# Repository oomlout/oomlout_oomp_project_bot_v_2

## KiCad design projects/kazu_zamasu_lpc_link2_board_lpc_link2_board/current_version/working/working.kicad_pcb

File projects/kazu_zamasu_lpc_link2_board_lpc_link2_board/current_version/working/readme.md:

# lpc_link2_board
 
## summary 
* id: kazu_zamasu_lpc_link2_board_lpc_link2_board
* user: kazu_zamasu
* name: lpc_link2_board
* board: lpc_link2_board
* repo: https://github.com/Kazu-zamasu/LPC-Link2-Board
* src_file_repo_kicad_pcb: LPC-Link2-Board.kicad_pcb
* src_file_repo_kicad_pcb_link: https://github.com/Kazu-zamasu/LPC-Link2-Board/tree/master/LPC-Link2-Board.kicad_pcb

* src_file_repo_sch: LPC-Link2-Board.sch
* src_file_repo_sch_link: https://github.com/Kazu-zamasu/LPC-Link2-Board/tree/master/LPC-Link2-Board.sch
* full details link: https://github.com/oomlout/oomlout_oomp_project_bot_v_2/tree/main/projects/kazu_zamasu_lpc_link2_board_lpc_link2_board/current_version/working

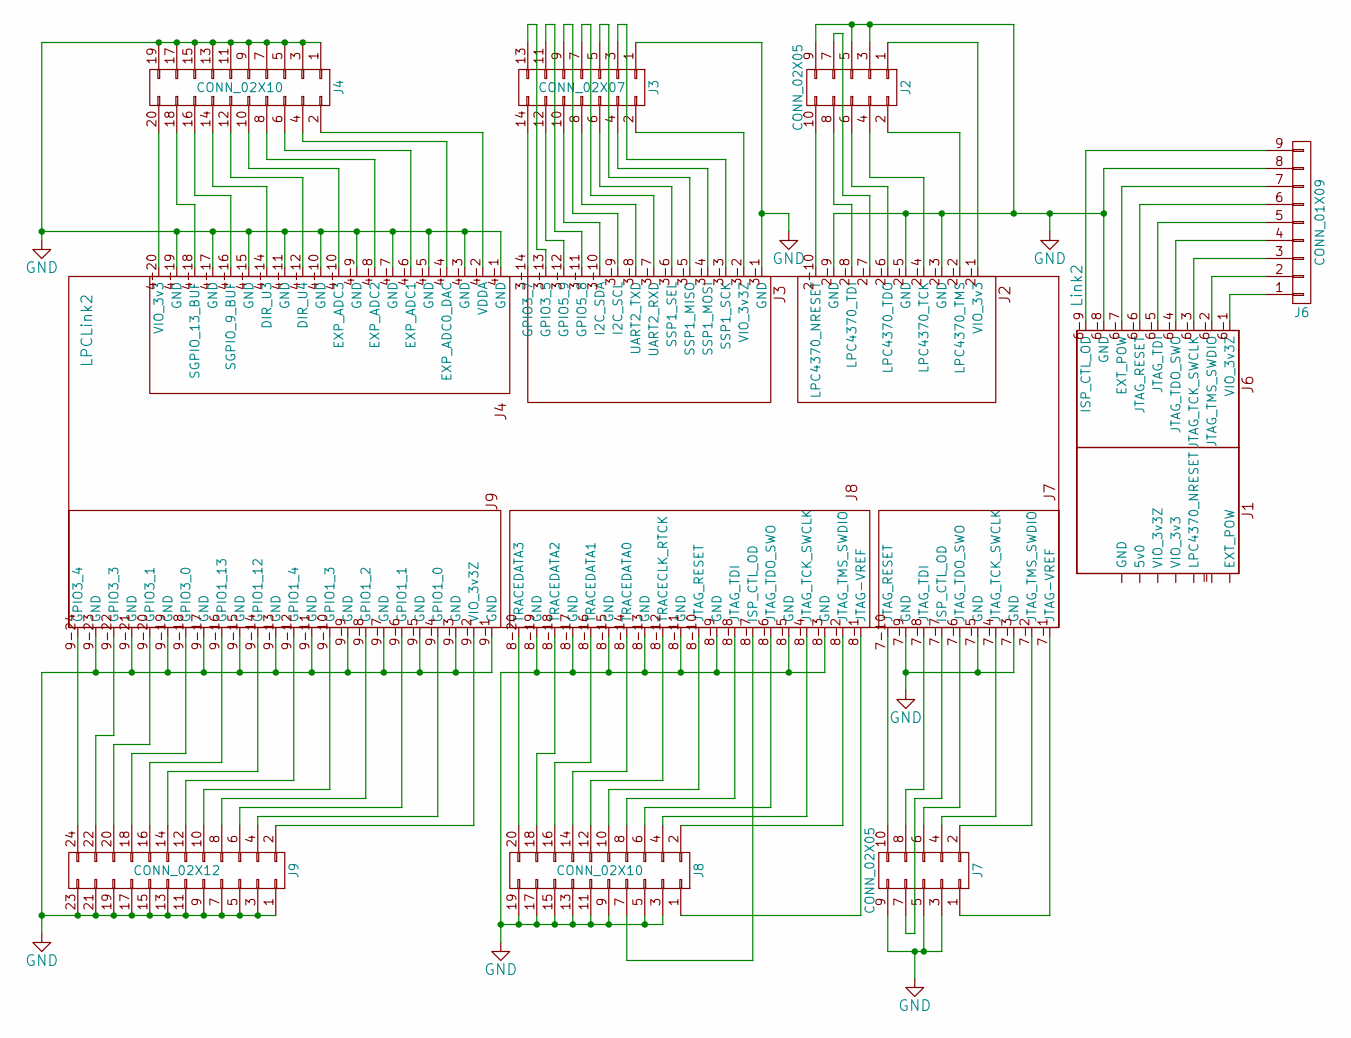
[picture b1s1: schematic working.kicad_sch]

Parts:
J2, J7: CONN_02X05; Socket_Strip_Straight_2x05
J3: CONN_02X07; Socket_Strip_Straight_2x07
J4, J8: CONN_02X10; Socket_Strip_Straight_2x10
J6: CONN_01X09; Socket_Strip_Straight_1x09
J9: CONN_02X12; Socket_Strip_Straight_2x12
Link2: LPCLink2; LPCLink2_Base-SMT

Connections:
unnamed: J2.1, Link2.2-1 (VIO_3v3)
unnamed: J2.2, Link2.2-2 (LPC4370_TMS)
unnamed: J2.4, Link2.2-4 (LPC4370_TCK)
unnamed: J2.6, Link2.2-6 (LPC4370_TDO)
unnamed: J2.7, Link2.2-7
unnamed: J2.8, Link2.2-8 (LPC4370_TDI)
unnamed: J2.10, Link2.2-10 (LPC4370_NRESET)
unnamed: J3.2, Link2.3-2 (VIO_3v3Z)
unnamed: J3.3, Link2.3-3 (SSP1_SCK)
unnamed: J3.4, Link2.3-4 (SSP1_MOSI)
unnamed: J3.5, Link2.3-5 (SSP1_MISO)
unnamed: J3.6, Link2.3-6 (SSP1_SEL)
unnamed: J3.7, Link2.3-7 (UART2_RXD)
unnamed: J3.8, Link2.3-8 (UART2_TXD)
unnamed: J3.9, Link2.3-9 (I2C_SCL)
unnamed: J3.10, Link2.3-10 (I2C_SDA)
unnamed: J3.11, Link2.3-11 (GPIO5_8)
unnamed: J3.12, Link2.3-12 (GPIO5_9)
unnamed: J3.13, Link2.3-13 (GPIO3_5)
unnamed: J3.14, Link2.3-14 (GPIO3_7)
unnamed: J4.2, Link2.4-2 (VDDA)
unnamed: J4.4, Link2.4-4 (EXP_ADC0_DAC)
unnamed: J4.6, Link2.4-6 (EXP_ADC1)
unnamed: J4.8, Link2.4-8 (EXP_ADC2)
unnamed: J4.12, Link2.4-12 (DIR_U4)
unnamed: J4.14, Link2.4-14 (DIR_U3)
unnamed: J4.16, Link2.4-16 (SGPIO_9_BUF)
unnamed: J4.18, Link2.4-18 (SGPIO_13_BUF)
unnamed: J4.20, Link2.4-20 (VIO_3v3)
unnamed: J6.1, Link2.6-1 (VIO_3v3Z)
unnamed: J6.2, Link2.6-2 (JTAG_TMS_SWDIO)
unnamed: J6.3, Link2.6-3 (JTAG_TCK_SWCLK)
unnamed: J6.4, Link2.6-4 (JTAG_TDO_SWO)
unnamed: J6.5, Link2.6-5 (JTAG_TDI)
unnamed: J6.6, Link2.6-6 (JTAG_RESET)
unnamed: J6.7, Link2.6-7 (EXT_POW)
unnamed: J6.9, Link2.6-9 (ISP_CTL_OD)
unnamed: J7.1, Link2.7-1 (JTAG-VREF)
unnamed: J7.2, Link2.7-2 (JTAG_TMS_SWDIO)
unnamed: J7.4, Link2.7-4 (JTAG_TCK_SWCLK)
unnamed: J7.6, Link2.7-6 (JTAG_TDO_SWO)
unnamed: J7.7, Link2.7-7 (ISP_CTL_OD)
unnamed: J7.8, Link2.7-8 (JTAG_TDI)
unnamed: J7.10, Link2.7-10 (JTAG_RESET)
unnamed: J8.1, Link2.8-1 (JTAG-VREF)
unnamed: J8.2, Link2.8-2 (JTAG_TMS_SWDIO)
unnamed: J8.4, Link2.8-4 (JTAG_TCK_SWCLK)
unnamed: J8.6, Link2.8-6 (JTAG_TDO_SWO)
unnamed: J8.7, Link2.8-7 (ISP_CTL_OD)
unnamed: J8.8, Link2.8-8 (JTAG_TDI)
unnamed: J8.10, Link2.8-10 (JTAG_RESET)
unnamed: J8.12, Link2.8-12 (TRACECLK_RTCK)
unnamed: J8.14, Link2.8-14 (TRACEDATA0)
unnamed: J8.16, Link2.8-16 (TRACEDATA1)
unnamed: J8.18, Link2.8-18 (TRACEDATA2)
unnamed: J8.20, Link2.8-20 (TRACEDATA3)
unnamed: J9.2, Link2.9-2 (VIO_3v3Z)
unnamed: J9.4, Link2.9-4 (GPIO1_0)
unnamed: J9.6, Link2.9-6 (GPIO1_1)
unnamed: J9.8, Link2.9-8 (GPIO1_2)
unnamed: J9.10, Link2.9-10 (GPIO1_3)
unnamed: J9.12, Link2.9-12 (GPIO1_4)
unnamed: J9.14, Link2.9-14 (GPIO1_12)
unnamed: J9.16, Link2.9-16 (GPIO1_13)
unnamed: J9.18, Link2.9-18 (GPIO3_0)
unnamed: J9.20, Link2.9-20 (GPIO3_1)
unnamed: J9.22, Link2.9-22 (GPIO3_3)
unnamed: J9.24, Link2.9-24 (GPIO3_4)

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
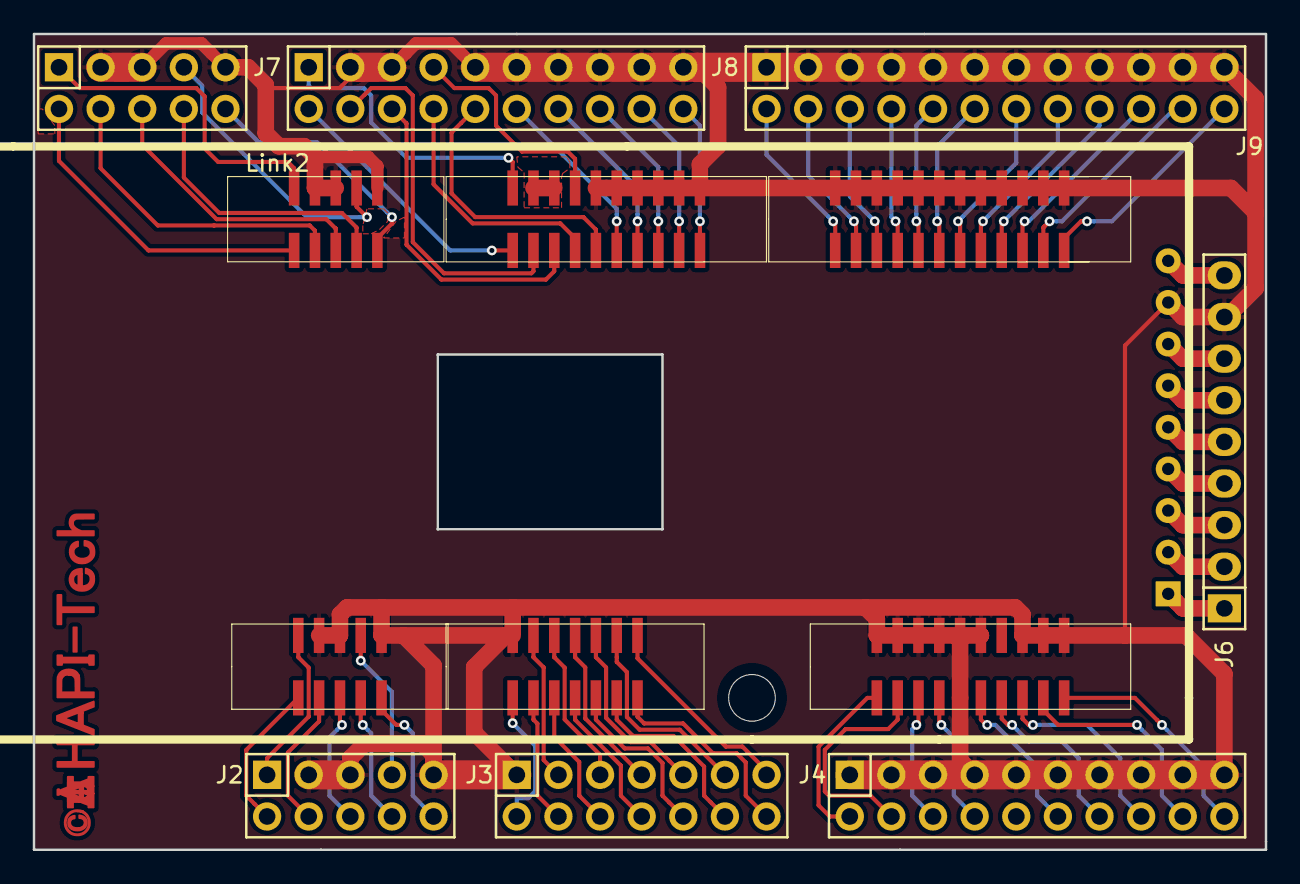
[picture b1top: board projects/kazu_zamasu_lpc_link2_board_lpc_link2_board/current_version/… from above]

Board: 2 copper layers, 75.2 x 49.8 mm, 8 parts (0 on the bottom side), 69 nets.

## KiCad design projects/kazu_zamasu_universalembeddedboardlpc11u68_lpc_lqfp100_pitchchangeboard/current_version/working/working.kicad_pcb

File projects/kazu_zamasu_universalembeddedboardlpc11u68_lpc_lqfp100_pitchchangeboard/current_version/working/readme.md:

# universalembeddedboardlpc11u68
 
## summary 
* id: kazu_zamasu_universalembeddedboardlpc11u68_lpc_lqfp100_pitchchangeboard
* user: kazu_zamasu
* name: universalembeddedboardlpc11u68
* board: lpc_lqfp100_pitchchangeboard
* repo: https://github.com/Kazu-zamasu/UniversalEmbeddedBoardLPC11U68
* src_file_repo_kicad_pcb: KiCad-files/LPC-LQFP100-PitchChangeBoard.kicad_pcb
* src_file_repo_kicad_pcb_link: https://github.com/Kazu-zamasu/UniversalEmbeddedBoardLPC11U68/tree/master/KiCad-files/LPC-LQFP100-PitchChangeBoard.kicad_pcb

* src_file_repo_sch: KiCad-files/LPC-LQFP100-PitchChangeBoard.sch
* src_file_repo_sch_link: https://github.com/Kazu-zamasu/UniversalEmbeddedBoardLPC11U68/tree/master/KiCad-files/LPC-LQFP100-PitchChangeBoard.sch
* full details link: https://github.com/oomlout/oomlout_oomp_project_bot_v_2/tree/main/projects/kazu_zamasu_universalembeddedboardlpc11u68_lpc_lqfp100_pitchchangeboard/current_version/working

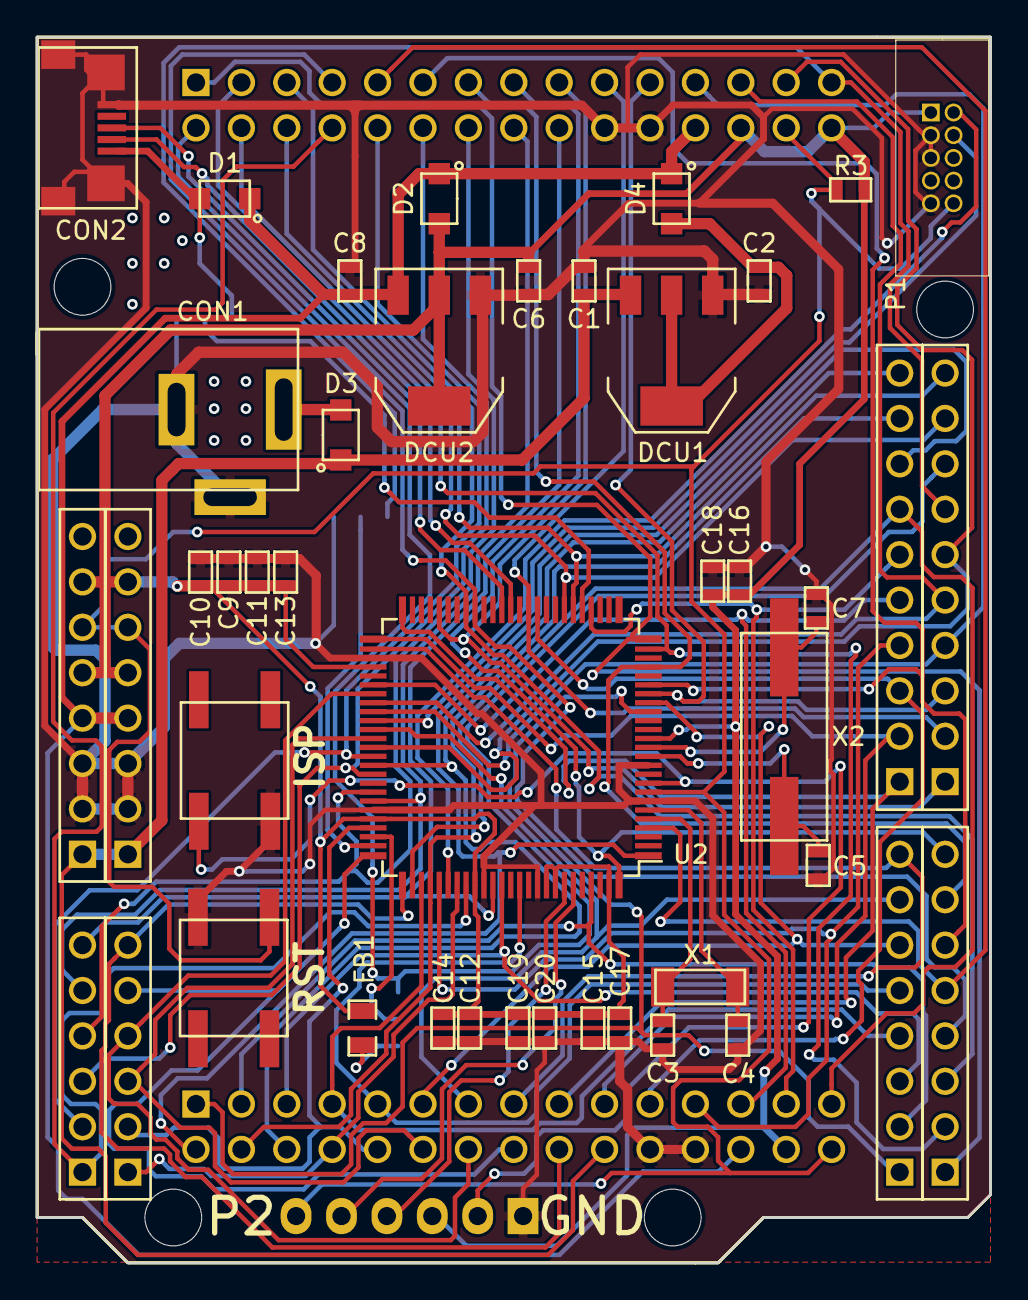
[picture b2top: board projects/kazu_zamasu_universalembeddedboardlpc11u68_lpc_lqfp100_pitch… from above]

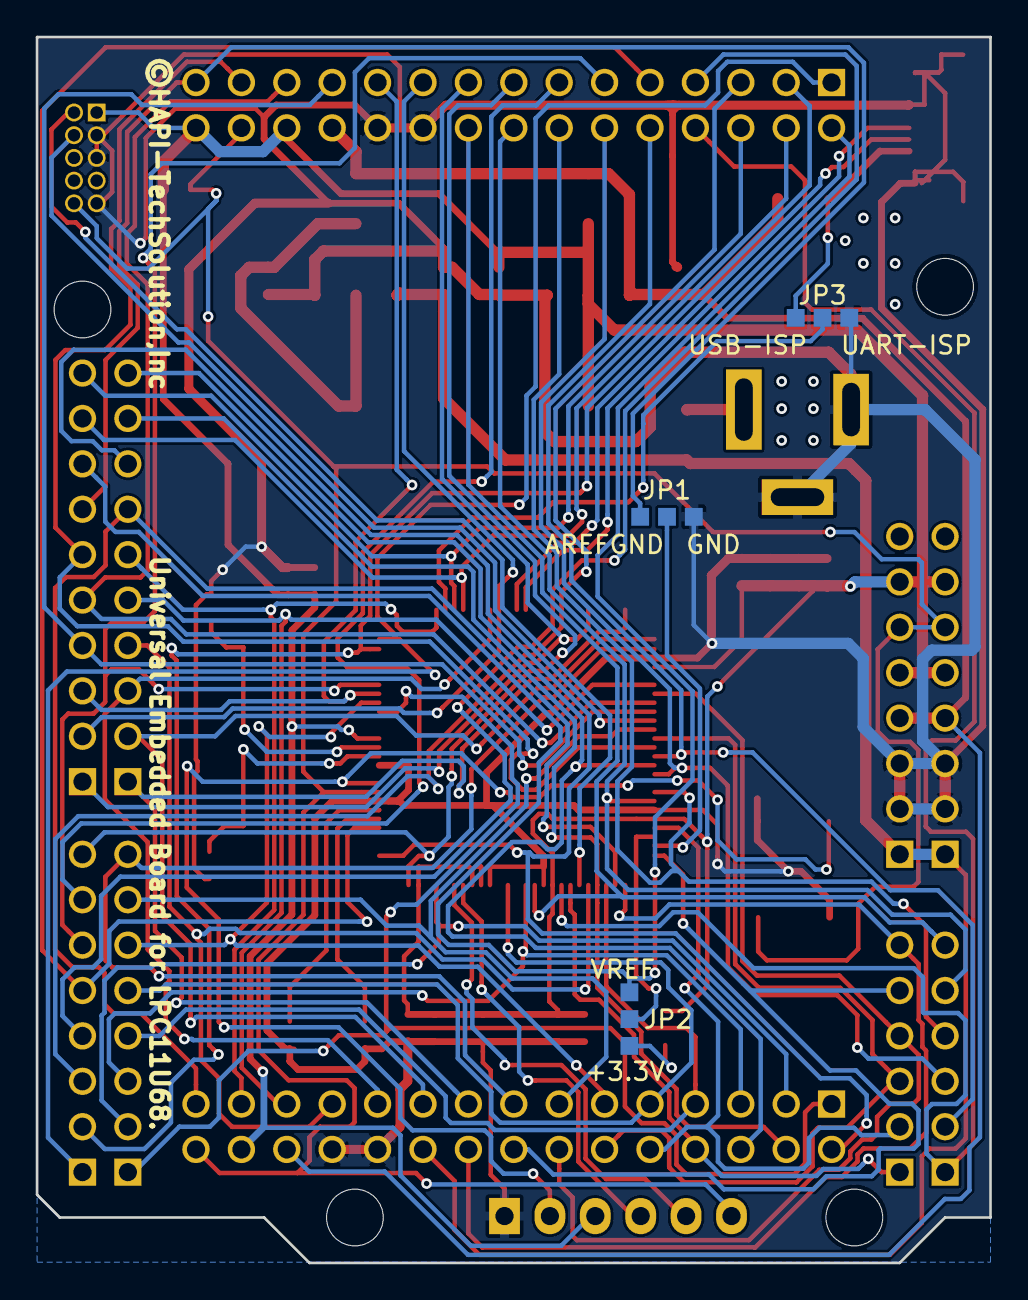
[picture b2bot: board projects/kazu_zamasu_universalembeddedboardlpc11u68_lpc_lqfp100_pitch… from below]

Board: 2 copper layers, 53.3 x 68.6 mm, 42 parts (5 on the bottom side), 71 nets.

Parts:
C1, C2, C6, C8, C17: 1uF; SMD-0603
C3, C4: 18pF; SMD-0603
C5, C7: 27pF; SMD-0603
C9, C11, C12, C15, C18, C19: 0.1uF; SMD-0603
C10, C13, C14, C16, C20: 0.01uF; SMD-0603
CON1: MJ-179P; DCJack_MJ-179P
CON2: HIROSE ZX62R-B-5P; Hirose-microUSB-ZX62R-B-5P
D1, D2, D3, D4: PMEG2010ER,115
DCU1: AZ1117E-5.0V; SOT-223
DCU2: AZ1117E-3.3V; SOT-223
FB1: R; SMD-0805
JP1, JP2, JP3: JUMPER3; SJ-3Pin
OPT1: Arduino-Shiled2(11x)Inside; Arduino-Shield-Inside-Outline
OPT2: Arduino-Shiled; Arduino-Shield-Normal-Outline
P1: CONN_02X05; JTAG-Half-2x5
P2: CONN_01X06; Pin_Header_Angled_1x06
R3: 100k; SMD-0603
SW1, SW2: SW_PUSH; SW_TACT-EVQQ2Y03W
U2: LPC11U68JBD100; LPC11E68-TQFP-100
X1: 32.768KHZ; FC-255-RTC-Xtal
X2: 12MHz; HC-49_S

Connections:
+3V3: C6.1, C9.1, C10.1, C11.1, C12.1, C13.1, C14.1, C15.1, C16.1, C17.1, C18.2, C19.1, C20.1, D2.1, DCU2.2, DCU2.4, FB1.1, OPT1.28, OPT1.30, OPT2.28, OPT2.30, P1.1, P2.3, R3.2, U2.14, U2.54, U2.71, U2.84, U2.92, U2.93, U2.99
+5V: C8.1, D1.2, D2.2, D4.2, DCU2.3, OPT1.27, OPT2.27
AREFGND: JP1.3, OPT2.14
GND: C1.1, C2.1, C3.2, C4.1, C5.2, C6.2, C7.1, C8.2, C9.2, C10.2, C11.2, C12.2, C13.2, C14.2, C15.2, C16.2, C17.2, C18.1, C19.2, C20.2, CON1.2, CON1.3, CON2.5, CON2.6, CON2.7, CON2.8, CON2.9, DCU1.1, DCU2.1, JP1.1, JP3.3, OPT1.25, OPT1.26, OPT2.25, OPT2.26, P1.3, P1.5, P1.9, P2.1, SW1.2, SW2.2, U2.7, U2.11, U2.53, U2.70, U2.85, U2.91
ISP: P2.2, SW2.1, U2.9
unnamed: C2.2, D4.1, DCU1.2, DCU1.4
unnamed: C3.1, U2.5, X1.1
unnamed: C4.2, U2.6, X1.2
unnamed: C5.1, U2.12, X2.1
unnamed: C7.2, U2.13, X2.2
unnamed: CON1.1, D3.1
unnamed: FB1.2, JP2.1
unnamed: JP1.2, U2.74
unnamed: JP2.2, U2.73
PIO0_2: OPT2.10, U2.19
PIO0_3(USB_VBUS): JP3.2, U2.30
PIO0_4: OPT2.17, U2.31
PIO0_5: OPT2.16, U2.32
PIO0_8: OPT2.12, U2.58
PIO0_9: OPT2.11, U2.59
PIO0_11: OPT2.19, U2.64
PIO0_12: OPT2.20, U2.66
PIO0_13: OPT2.21, U2.68
PIO0_14: OPT2.22, U2.69
PIO0_16: OPT1.18, U2.82
PIO0_18: P2.4, U2.94
PIO0_19: P2.5, U2.95
PIO0_20: OPT1.0, U2.17
PIO0_22: OPT1.20, U2.62
PIO0_23: OPT2.18, U2.83
PIO1_0: OPT1.1, U2.97
PIO1_3: OPT1.19, U2.72
PIO1_8: OPT1.6, U2.61
PIO1_9: OPT2.23, U2.86
PIO1_10: OPT1.5, U2.18
PIO1_11: OPT1.17, U2.65
PIO1_12: OPT1.4, U2.89
PIO1_13: OPT1.3, U2.78
PIO1_14: OPT1.16, U2.79
PIO1_15: OPT1.2, U2.87
PIO1_18: OPT2.2, U2.43
PIO1_19: OPT2.4, U2.4
PIO1_20: OPT1.13, U2.29
PIO1_21: OPT1.12, U2.56
PIO1_22: OPT1.11, U2.80
PIO1_23: OPT1.10, U2.35
PIO1_24: OPT2.3, U2.42
PIO1_25: OPT2.7, U2.100
PIO1_26: OPT2.5, U2.20
PIO1_27: OPT2.6, U2.22
PIO1_28: OPT2.8, U2.46
PIO1_29: OPT2.13, U2.63
PIO2_3: OPT2.9, U2.36
PIO2_11: OPT2.0, U2.25
PIO2_12: OPT2.1, U2.24
PIO2_16: OPT1.8, U2.50
PIO2_17: OPT1.9, U2.51
PIO2_18: OPT1.7, U2.52
PIO2_19: OPT1.21, U2.57
PIO2_20: OPT1.22, U2.75
PIO2_21: OPT1.23, U2.76
PIO2_22: OPT1.14, U2.77
PIO2_23: OPT1.15, U2.1
RESETn: OPT1.29, OPT2.29, P1.10, P2.6, R3.1, SW1.1, U2.8
SWCLK: P1.4, U2.60
SWDIO: P1.2, U2.81
USB-VDD: CON2.1, D1.1, JP3.1
USB_DM: CON2.2, U2.38
USB_DP: CON2.3, U2.39
VREF: JP2.3, OPT2.15
Vin: C1.2, D3.2, DCU1.3, OPT1.24, OPT2.24

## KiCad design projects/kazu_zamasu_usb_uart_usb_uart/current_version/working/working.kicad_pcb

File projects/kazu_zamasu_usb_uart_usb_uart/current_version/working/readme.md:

# usb_uart
 
## summary 
* id: kazu_zamasu_usb_uart_usb_uart
* user: kazu_zamasu
* name: usb_uart
* board: usb_uart
* repo: https://github.com/Kazu-zamasu/USB-UART
* src_file_repo_kicad_pcb: USB-UART.kicad_pcb
* src_file_repo_kicad_pcb_link: https://github.com/Kazu-zamasu/USB-UART/tree/master/USB-UART.kicad_pcb

* src_file_repo_sch: USB-UART.sch
* src_file_repo_sch_link: https://github.com/Kazu-zamasu/USB-UART/tree/master/USB-UART.sch
* full details link: https://github.com/oomlout/oomlout_oomp_project_bot_v_2/tree/main/projects/kazu_zamasu_usb_uart_usb_uart/current_version/working

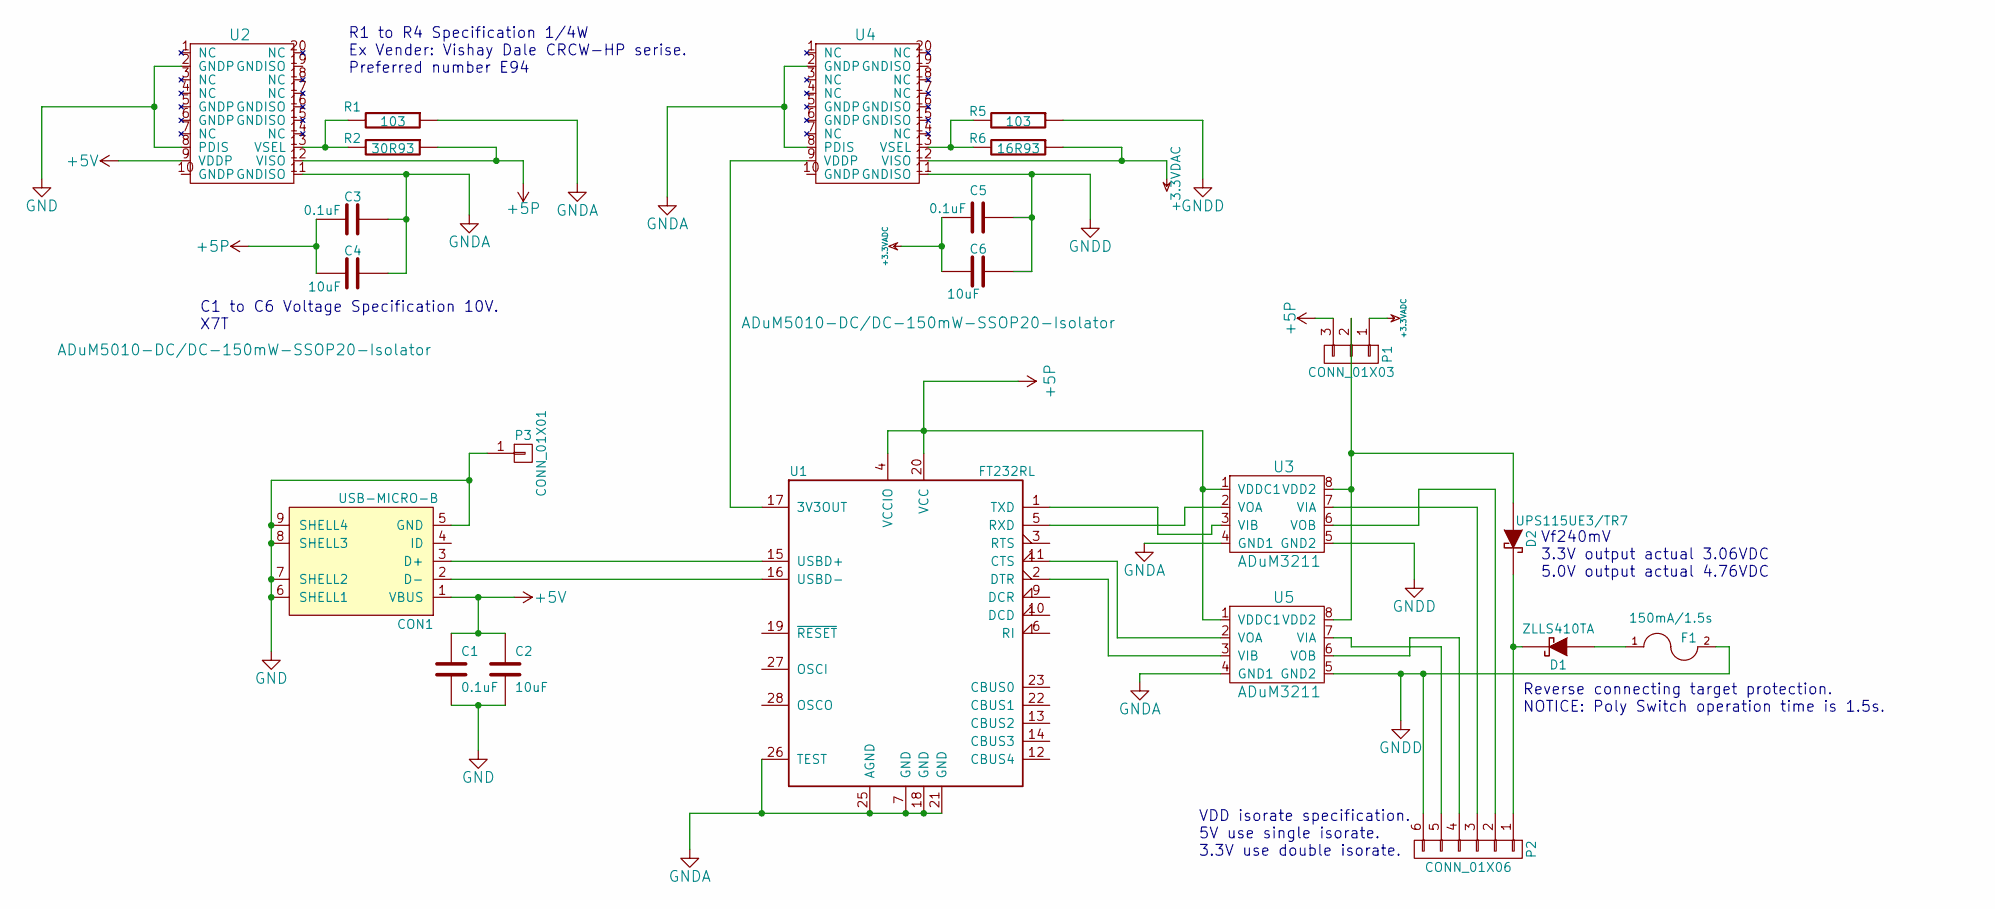
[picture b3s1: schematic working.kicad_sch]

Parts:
C1, C3, C5: 0.1uF; SMD-0603_c
C2, C4, C6: 10uF; SMD-0603_c
CON1: USB-MICRO-B; Hirose-microUSB-ZX62R-B-5P
D1: ZLLS410TA; ZLLS410
D2: UPS115UE3/TR7; UPS115UE3_TR7
F1: 150mA/1.5s; SMD-1210
P1: CONN_01X03
P2: CONN_01X06; Socket_Strip_Angled_1x06
P3: CONN_01X01; EarthPad
R1, R5: 103; SMD-0603_r
R2: 30R93; SMD-0603_r
R6: 16R93; SMD-0603_r
U1: FT232RL; SSOP-28_5.3x10.2mm_Pitch0.65mm
U2, U4: ADuM5010-DC/DC-150mW-SSOP20-Isolator; SSOP-20_5.3x7.2mm_Pitch0.65mm
U3, U5: ADuM3211; SOIC-8_3.9x4.9mm_Pitch1.27mm

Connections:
+3.3VADC: C5.2, C6.2, P1.1
+3.3VDAC: R6.1, U4.12 (VISO)
+5P: C3.2, C4.2, P1.3, R2.1, U1.4 (VCCIO), U1.20 (VCC), U2.12 (VISO), U3.1 (VDDC1), U5.1 (VDDC1)
+5V: C1.1, C2.1, CON1.1 (VBUS), U2.9 (VDDP)
GND: C1.2, C2.2, CON1.5 (GND), CON1.6 (SHELL1), CON1.7 (SHELL2), CON1.8 (SHELL3), CON1.9 (SHELL4), P3.1, U2.2 (GNDP), U2.8 (PDIS)
GNDA: C3.1, C4.1, R1.1, U1.7 (GND), U1.18 (GND), U1.21 (GND), U1.25 (AGND), U1.26 (TEST), U2.11 (GNDISO), U3.4 (GND1), U4.2 (GNDP), U4.8 (PDIS), U5.4 (GND1)
GNDD: C5.1, C6.1, F1.2, P2.6, R5.1, U3.5 (GND2), U4.11 (GNDISO), U5.5 (GND2)
unnamed: CON1.2 (D-), U1.16 (USBD-)
unnamed: CON1.3 (D+), U1.15 (USBD+)
unnamed: D1.1 (A), F1.1
unnamed: D1.2 (K), D2.2 (K), P2.1
unnamed: D2.1 (A), P1.2, U3.8 (VDD2), U5.8 (VDD2)
unnamed: P2.2, U3.6 (VOB)
unnamed: P2.3, U3.7 (VIA)
unnamed: P2.4, U5.6 (VOB)
unnamed: P2.5, U5.7 (VIA)
unnamed: R1.2, R2.2, U2.13 (VSEL)
unnamed: R5.2, R6.2, U4.13 (VSEL)
unnamed: U1.1 (TXD), U3.3 (VIB)
unnamed: U1.2 (DTR), U5.3 (VIB)
unnamed: U1.5 (RXD), U3.2 (VOA)
unnamed: U1.11 (CTS), U5.2 (VOA)
unnamed: U1.17 (3V3OUT), U4.9 (VDDP)

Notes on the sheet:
Reverse connecting target protection. NOTICE: Poly Switch operation time is 1.5s.
C1 to C6 Voltage Specification 10V. X7T
Vf240mV 3.3V output actual 3.06VDC 5.0V output actual 4.76VDC
VDD isorate specification. 5V use single isorate. 3.3V use double isorate.
R1 to R4 Specification 1/4W Ex Vender: Vishay Dale CRCW-HP serise. Preferred number E94

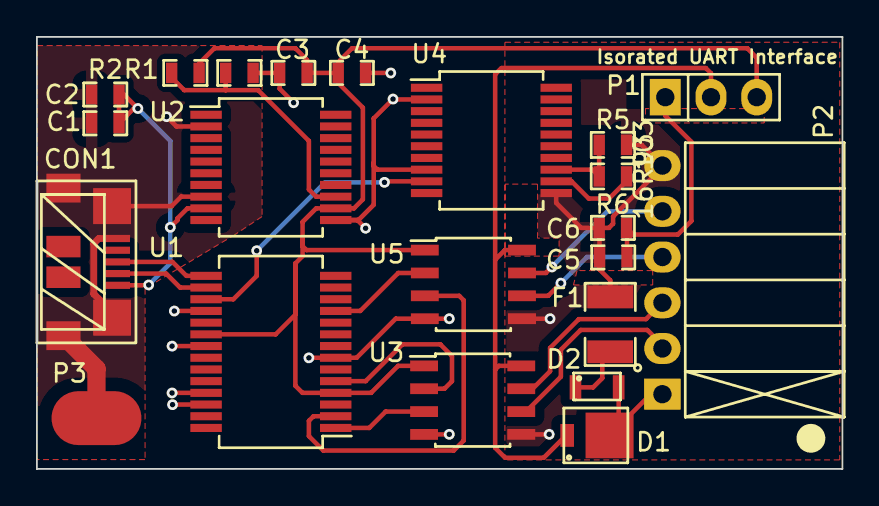
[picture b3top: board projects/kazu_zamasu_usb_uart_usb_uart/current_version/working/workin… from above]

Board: 2 copper layers, 44.8 x 24.0 mm, 22 parts (0 on the bottom side), 23 nets.

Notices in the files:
projects/kazu_zamasu_universalembeddedboardlpc11u68_lpc_lqfp100_pitchchangeboard/current_version/working/working.kicad_pcb:
©HAPI-TechSolution,Inc
